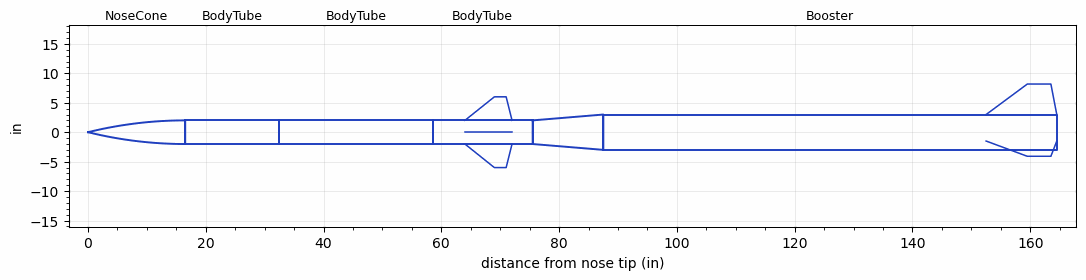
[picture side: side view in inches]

<RASAeroDocument>
 <FileVersion>2</FileVersion>
 <RocketDesign>
  <NoseCone>
   <Length>16.5</Length>
   <Diameter>4.014</Diameter>
   <Shape>Tangent Ogive</Shape>
   <Location>0</Location>
  </NoseCone>
  <BodyTube>
   <Length>16</Length>
   <Diameter>4.014</Diameter>
   <Location>16.5</Location>
  </BodyTube>
  <BodyTube>
   <Length>26</Length>
   <Diameter>4.014</Diameter>
   <Location>32.5</Location>
  </BodyTube>
  <BodyTube>
   <Length>17</Length>
   <Diameter>4.014</Diameter>
   <Location>58.5</Location>
   <Fin>
    <Count>4</Count>
    <Chord>8</Chord>
    <Span>4</Span>
    <SweepDistance>5</SweepDistance>
    <TipChord>2</TipChord>
    <Thickness>0.125</Thickness>
    <Location>11.5</Location>
    <AirfoilSection>Hexagonal</AirfoilSection>
    <FX1>0.0625</FX1>
    <FX3>0.0625</FX3>
   </Fin>
  </BodyTube>
  <Booster>
   <Length>77</Length>
   <Diameter>6</Diameter>
   <InsideDiameter>4.014</InsideDiameter>
   <Location>75.5</Location>
   <ShoulderLength>12</ShoulderLength>
   <Fin>
    <Count>3</Count>
    <Chord>12</Chord>
    <Span>5.18</Span>
    <SweepDistance>7</SweepDistance>
    <TipChord>4</TipChord>
    <Thickness>0.125</Thickness>
    <Location>12</Location>
    <AirfoilSection>Hexagonal</AirfoilSection>
    <FX1>0.0625</FX1>
    <FX3>0.0625</FX3>
   </Fin>
  </Booster>
  <Surface>Smooth Paint</Surface>
  <ModifiedBarrowman>True</ModifiedBarrowman>
  <Turbulence>False</Turbulence>
  <SustainerNozzle>0.75</SustainerNozzle>
  <Booster1Nozzle>1.25</Booster1Nozzle>
  <UseBooster1>True</UseBooster1>
  <UseBooster2>False</UseBooster2>
 </RocketDesign>
 <LaunchSite>
  <Altitude>0</Altitude>
  <Pressure>0</Pressure>
  <RodAngle>0</RodAngle>
  <RodLength>12</RodLength>
  <Temperature>30</Temperature>
  <WindSpeed>5</WindSpeed>
 </LaunchSite>
 <Recovery>
  <Altitude1>1000</Altitude1>
  <Altitude2>1000</Altitude2>
  <DeviceType1>None</DeviceType1>
  <DeviceType2>None</DeviceType2>
  <Event1>False</Event1>
  <Event2>False</Event2>
  <Size1>1</Size1>
  <Size2>1</Size2>
  <EventType1>None</EventType1>
  <EventType2>None</EventType2>
  <CD1>1.33</CD1>
  <CD2>1.33</CD2>
 </Recovery>
 <SimulationList>
  <Simulation>
   <SustainerEngine>I435T  (AT)</SustainerEngine>
   <SustainerLaunchWt>10.3</SustainerLaunchWt>
   <SustainerNozzleDiameter>0.75</SustainerNozzleDiameter>
   <SustainerCG>48.74</SustainerCG>
   <SustainerIgnitionDelay>2</SustainerIgnitionDelay>
   <Booster1Engine>K1440  (CTI)</Booster1Engine>
   <Booster1LaunchWt>35.3</Booster1LaunchWt>
   <Booster1SeparationDelay>1</Booster1SeparationDelay>
   <Booster1IgnitionDelay>0</Booster1IgnitionDelay>
   <Booster1CG>89.32</Booster1CG>
   <Booster1NozzleDiameter>1.25</Booster1NozzleDiameter>
   <IncludeBooster1>True</IncludeBooster1>
   <Booster2Delay>0</Booster2Delay>
   <IncludeBooster2>False</IncludeBooster2>
   <TimetoApogee>20.96032</TimetoApogee>
   <MaxAltitude>6406.749</MaxAltitude>
   <MaxVelocity>658.2751</MaxVelocity>
  </Simulation>
  <Simulation>
   <SustainerEngine>I435T  (AT)</SustainerEngine>
   <SustainerLaunchWt>10.3</SustainerLaunchWt>
   <SustainerNozzleDiameter>0.75</SustainerNozzleDiameter>
   <SustainerCG>48.74</SustainerCG>
   <SustainerIgnitionDelay>2</SustainerIgnitionDelay>
   <Booster1Engine>L1050-BS-P  (CTI)</Booster1Engine>
   <Booster1LaunchWt>37.8</Booster1LaunchWt>
   <Booster1SeparationDelay>1</Booster1SeparationDelay>
   <Booster1IgnitionDelay>0</Booster1IgnitionDelay>
   <Booster1CG>94.41</Booster1CG>
   <Booster1NozzleDiameter>1.875</Booster1NozzleDiameter>
   <IncludeBooster1>True</IncludeBooster1>
   <Booster2Delay>0</Booster2Delay>
   <IncludeBooster2>False</IncludeBooster2>
   <TimetoApogee>24.03036</TimetoApogee>
   <MaxAltitude>8467.993</MaxAltitude>
   <MaxVelocity>756.8294</MaxVelocity>
  </Simulation>
 </SimulationList>
</RASAeroDocument>
